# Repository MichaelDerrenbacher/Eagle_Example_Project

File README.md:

# Eagle_Example_Project
Second order lowpass filter with output buffer schematic and layout

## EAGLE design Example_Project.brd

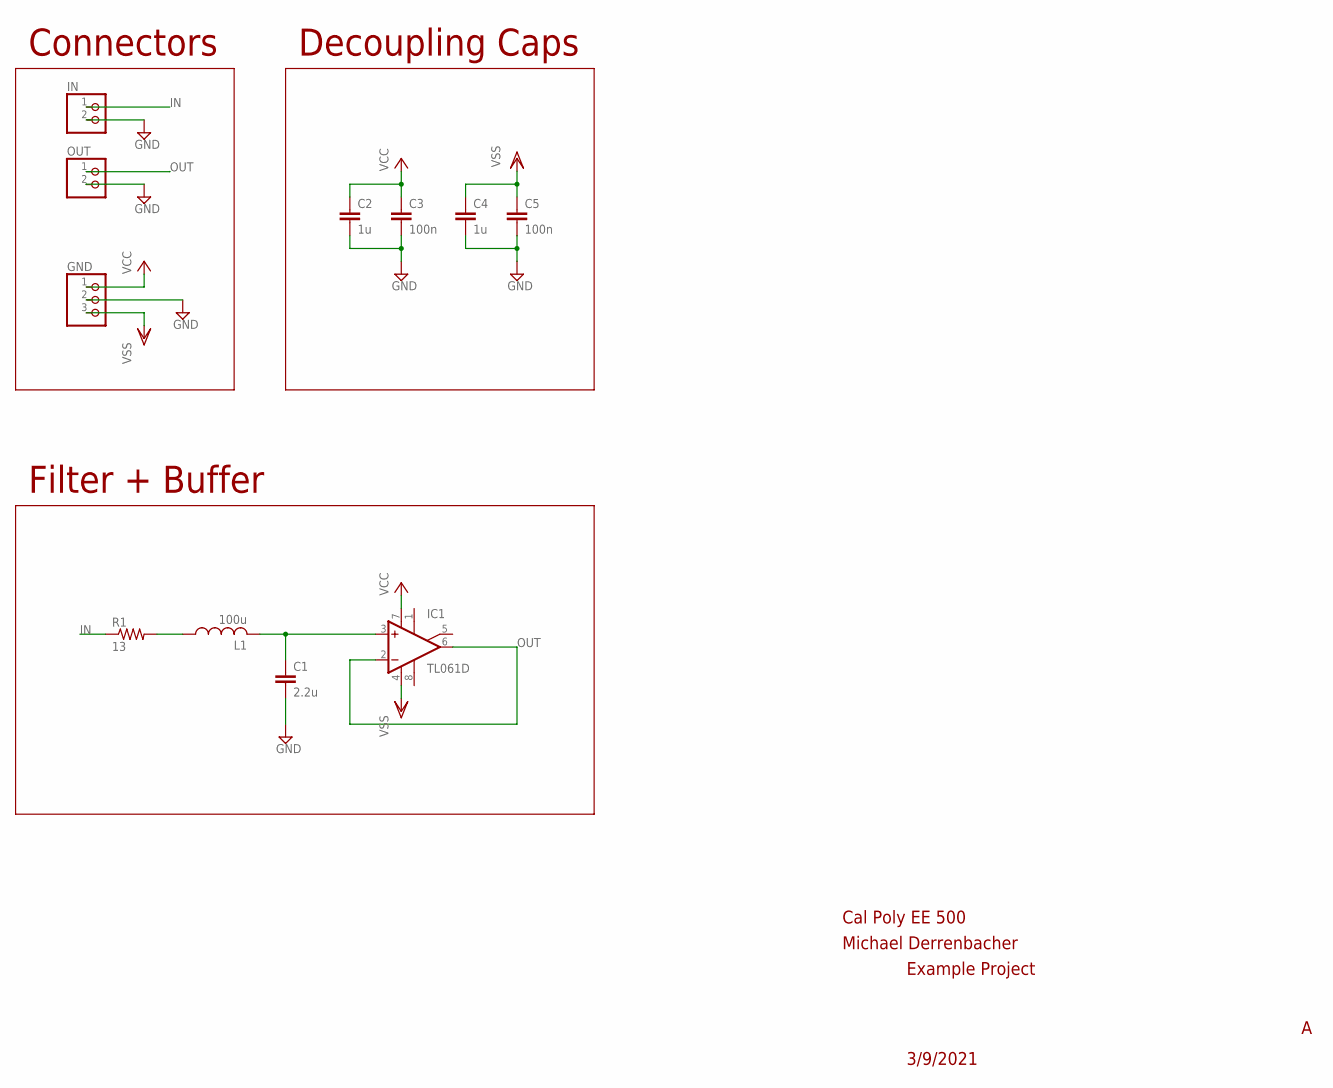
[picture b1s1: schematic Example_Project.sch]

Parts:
C1: 2.2u; C0805
C2, C4: 1u; C0805
C3, C5: 100n; C0805
GND: PINHD-1X3; 1X03
IC1: TL061D; SO08
IN: PINHD-1X2; 1X02
L1: 100u; L1812
OUT: PINHD-1X2; 1X02
R1: 13; R0805

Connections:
GND: C1.2, C2.2, C3.2, C4.2, C5.2, GND.2, IN.2, OUT.2
IN: IN.1, R1.1
unnamed: L1.1, R1.2
unnamed: C1.1, IC1.3 (+IN), L1.2
OUT: IC1.2 (-IN), IC1.6 (OUT), OUT.1
VCC: C2.1, C3.1, GND.1, IC1.7 (V+)
VSS: C4.1, C5.1, GND.3, IC1.4 (V-)

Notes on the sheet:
Example Project
3/9/2021
Michael Derrenbacher
Cal Poly EE 500
Filter + Buffer
Connectors
Decoupling Caps

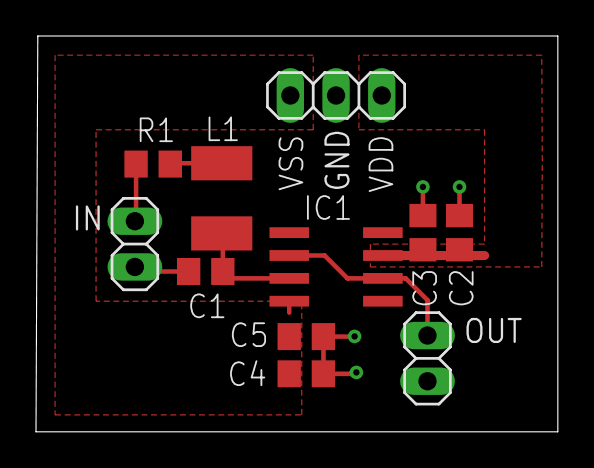
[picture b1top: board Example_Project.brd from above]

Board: 2 copper layers, 29.0 x 22.0 mm, 11 parts (0 on the bottom side), 7 nets.

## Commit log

2021-03-11 Eagle Project Folder Upload
